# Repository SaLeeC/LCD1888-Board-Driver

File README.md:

# LCD1888-Board-Driver
Board to drive LCD 3 digit 1/2 (DE113) with HT1621B

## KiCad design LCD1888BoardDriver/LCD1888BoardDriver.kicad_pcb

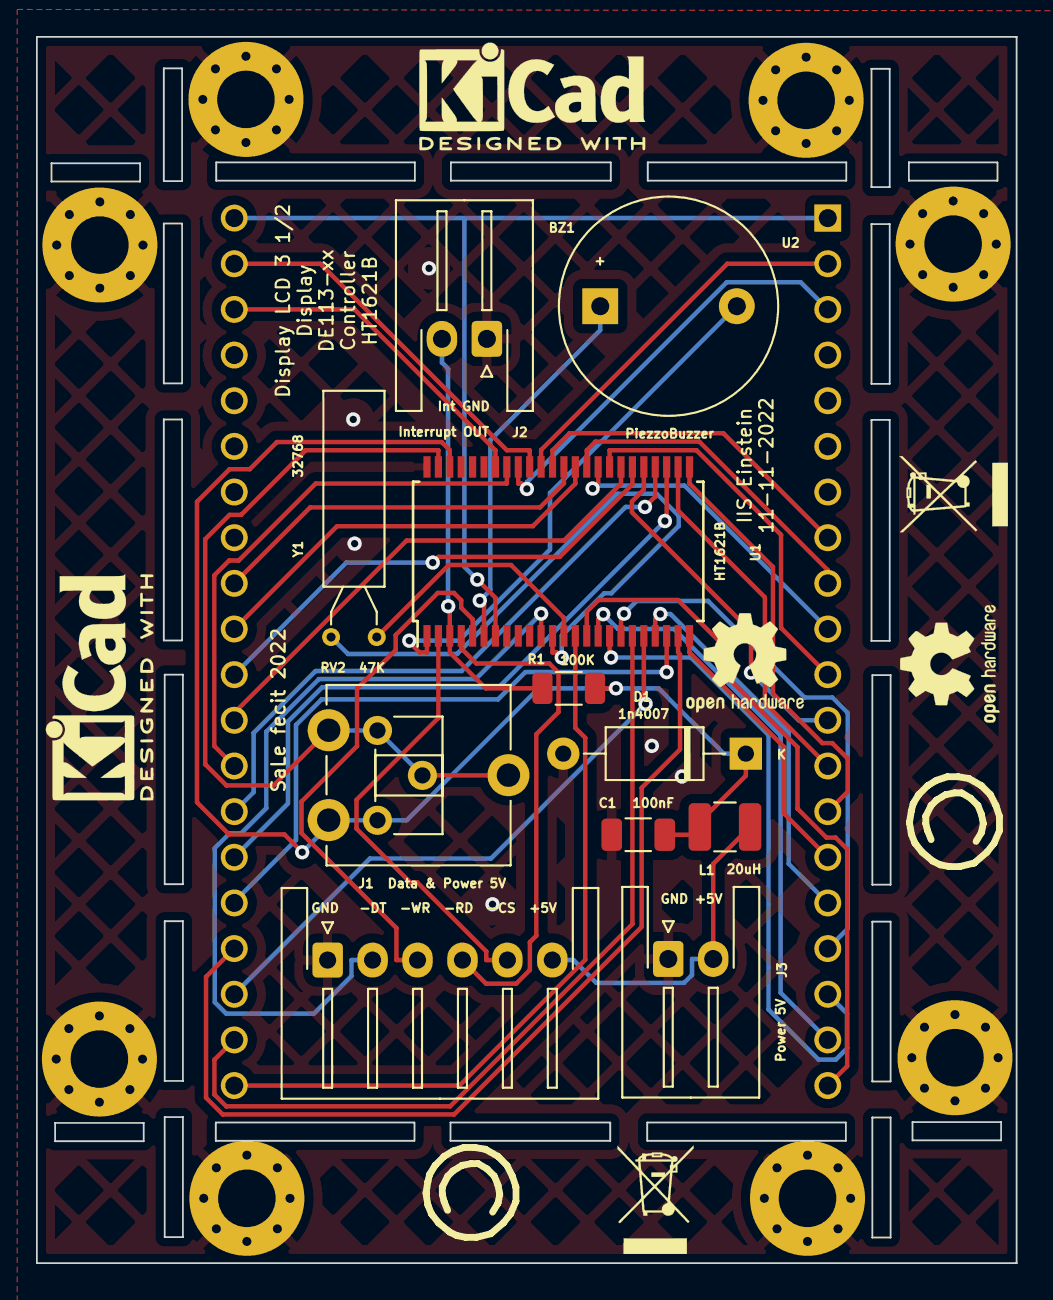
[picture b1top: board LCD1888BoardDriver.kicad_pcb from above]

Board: 2 copper layers, 54.5 x 68.2 mm, 29 parts (1 on the bottom side), 43 nets.

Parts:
BZ1: PiezzoBuzzer; Buzzer_12x9.5RM7.6
C1: 100nF; C_1206_3216Metric
D1: 1n4007; D_A-405_P10.16mm_Horizontal
H1, H2, H3, H4, H8, H9, H10, H11: MountingHole_Pad; MountingHole_3.2mm_M3_Pad_Via
H5, H12: MountingHole; KiCad-Logo2_5mm_SilkScreen
H6, H13: MountingHole; OSHW-Logo2_7.3x6mm_SilkScreen
H7, H14: MountingHole; Symbol_CC-ShareAlike_SilkscreenTop_Small
H15, H16: MountingHole; WEEE-Logo_4.2x6mm_SilkScreen
J1: Data & Power 5V; JST_XH_S6B-XH-A-1_1x06_P2.50mm_Horizontal
J2: Interrupt OUT; JST_XH_S2B-XH-A-1_1x02_P2.50mm_Horizontal
J3: Power 5V; JST_XH_S2B-XH-A-1_1x02_P2.50mm_Horizontal
L1: 20uH; L_1210_3225Metric
R1: 100K; R_1206_3216Metric
RV1: 47K; Potentiometer_ACP_CA6-H2,5_Horizontal
RV2: 47K; Potentiometer_ACP_CA9-V10_Vertical
U1: HT1621B; SSOP-48_7.5x15.9mm_P0.635mm
U2: DE113-XX-XX
Y1: 32768; Crystal_AT310_D3.0mm_L10.0mm_Horizontal

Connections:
GND: C1.2, D1.2 (A), H1.1, H2.1, H3.1, H4.1, H8.1, H9.1, H10.1, H11.1, J1.1, J2.1, J3.1, U1.48 (VSS)
unnamed: BZ1.1 (-), U1.6 (BZ)
unnamed: BZ1.2 (+), U1.1 (~BZ)
unnamed: C1.1, D1.1 (K), L1.1, R1.2, RV1.3, RV2.1, U1.46 (VDD)
unnamed: J2.2, R1.1, U1.3 (~IRQ)
unnamed: J1.6, J3.2, L1.2
unnamed: RV1.1, RV1.2, RV2.2, RV2.3, U1.47 (VLCD)
unnamed: J1.5, U1.2 (~CS)
unnamed: J1.4, U1.4 (~RD)
unnamed: J1.3, U1.5 (~WR)
unnamed: U1.7 (COM0), U2.1 (BP), U2.40 (BP)
unnamed: J1.2, U1.11 (DATA)
unnamed: U1.12 (OSCI), Y1.2
unnamed: U1.13 (OSCO), Y1.1
unnamed: U1.14 (SEG0), U2.21 (3A)
unnamed: U1.15 (SEG1), U2.20 (3B)
unnamed: U1.16 (SEG2), U2.19 (3C)
unnamed: U1.17 (SEG3), U2.18 (3D)
unnamed: U1.18 (SEG4), U2.17 (3E)
unnamed: U1.19 (SEG5), U2.22 (3F)
unnamed: U1.20 (SEG6), U2.23 (3G)
unnamed: U1.21 (SEG7), U2.16 (DP3)
unnamed: U1.22 (SEG8), U2.25 (2A)
unnamed: U1.23 (SEG9), U2.24 (2B)
unnamed: U1.24 (SEG10), U2.15 (2C)
unnamed: U1.25 (SEG11), U2.14 (2D)
unnamed: U1.26 (SEG12), U2.13 (2E)
unnamed: U1.27 (SEG13), U2.26 (2F)
unnamed: U1.28 (SEG14), U2.27 (2G)
unnamed: U1.29 (SEG15), U2.12 (DP2)
unnamed: U1.30 (SEG16), U2.30 (1A)
unnamed: U1.31 (SEG17), U2.29 (1B)
unnamed: U1.32 (SEG18), U2.11 (1C)
unnamed: U1.33 (SEG19), U2.10 (1D)
unnamed: U1.34 (SEG20), U2.9 (1E)
unnamed: U1.35 (SEG21), U2.31 (1F)
unnamed: U1.36 (SEG22), U2.32 (1G)
unnamed: U1.37 (SEG23), U2.8 (DP1)
unnamed: U1.38 (SEG24), U2.2 (-)
unnamed: U1.39 (SEG25), U2.39 (:)
unnamed: U1.40 (SEG26), U2.3 (K)
unnamed: U1.41 (SEG27), U2.28 (COL)
unnamed: U1.42 (SEG28), U2.38 (LO_BAT)

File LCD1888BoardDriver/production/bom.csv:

Designator,Footprint,Quantity,Value,LCSC Part #
BZ1,Buzzer_12x9.5RM7.6,1,PiezzoBuzzer,
C1,C_1206_3216Metric,1,100nF,
D1,D_A-405_P10.16mm_Horizontal,1,1n4007,
"H1, H10, H11, H2, H3, H4, H8, H9",MountingHole_3.2mm_M3_Pad_Via,8,MountingHole_Pad,
"H12, H5",KiCad-Logo2_5mm_SilkScreen,2,MountingHole,
"H13, H6",OSHW-Logo2_7.3x6mm_SilkScreen,2,MountingHole,
"H14, H7",Symbol_CC-ShareAlike_SilkscreenTop_Small,2,MountingHole,
"H15, H16",WEEE-Logo_4.2x6mm_SilkScreen,2,MountingHole,
J1,JST_XH_S6B-XH-A-1_1x06_P2.50mm_Horizontal,1,Data & Power 5V,
J2,JST_XH_S2B-XH-A-1_1x02_P2.50mm_Horizontal,1,Interrupt OUT,
J3,JST_XH_S2B-XH-A-1_1x02_P2.50mm_Horizontal,1,Power 5V,
L1,L_1210_3225Metric,1,20uH,
R1,R_1206_3216Metric,1,100K,
RV1,"Potentiometer_ACP_CA6-H2,5_Horizontal",1,47K,
RV2,Potentiometer_ACP_CA9-V10_Vertical,1,47K,
U1,SSOP-48_7.5x15.9mm_P0.635mm,1,HT1621B,
U2,DE113-XX-XX,1,DE113-XX-XX,
Y1,Crystal_AT310_D3.0mm_L10.0mm_Horizontal,1,32768,
